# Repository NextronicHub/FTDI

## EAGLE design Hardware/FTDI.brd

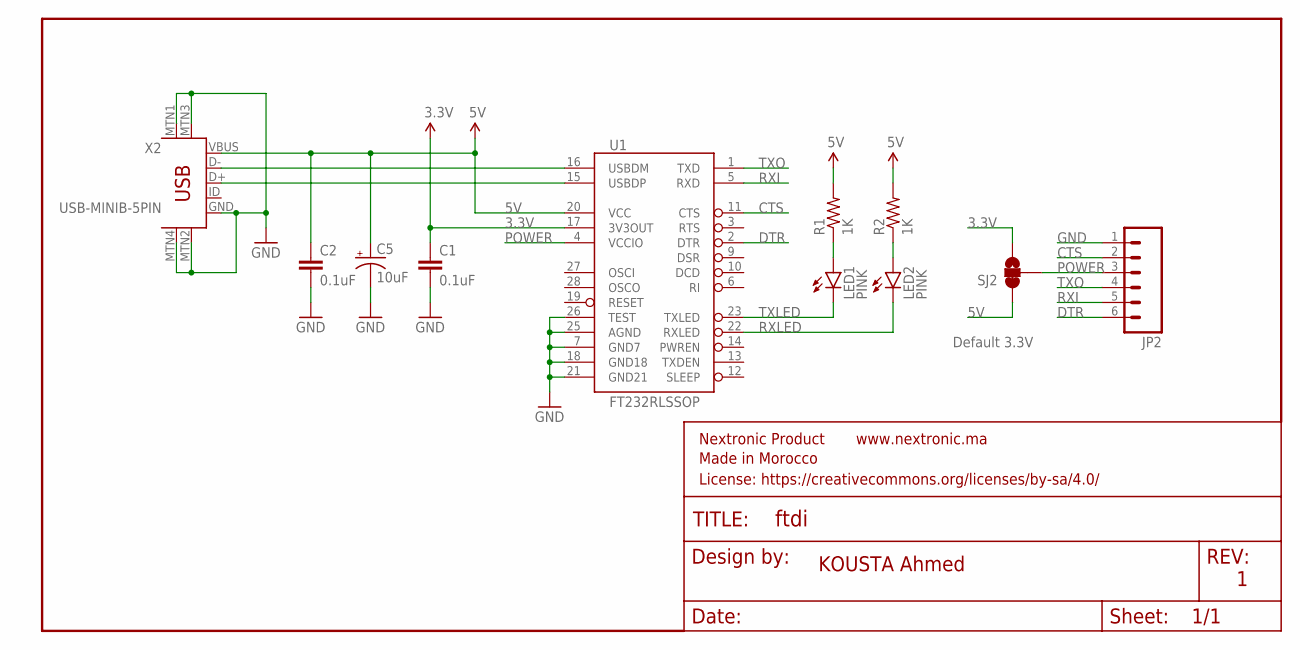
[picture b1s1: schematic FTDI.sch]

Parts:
C1, C2: 0.1uF; 0603-CAP
C5: 10uF; EIA3216
FRAME2: FRAME-LETTER; CREATIVE_COMMONS
JP2: M06SILK_FEMALE_PTH; 1X06
LED1, LED2: PINK; LED-1206
R1, R2: 1K; 0603-RES
SJ2: SOLDERJUMPER_2WAYS; SJ_3
U1: FT232RLSSOP; SSOP28DB
X2: USB-MINIB-5PIN; USB-MINIB

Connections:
3.3V: C1.1, SJ2.3, U1.17 (3V3OUT)
5V: C2.1, C5.A (+), R1.2, R2.2, SJ2.1, U1.20 (VCC), X2.VBUS
CTS: JP2.2, U1.11 (CTS)
DTR: JP2.6, U1.2 (DTR)
GND: C1.2, C2.2, C5.C (-), JP2.1, U1.7 (GND7), U1.18 (GND18), U1.21 (GND21), U1.25 (AGND), U1.26 (TEST), X2.GND, X2.MTN1 (MTN2), X2.MTN2 (MTN3), X2.MTN3 (MTN1), X2.MTN4
unnamed: LED1.A, R1.1
unnamed: LED2.A, R2.1
POWER: JP2.3, SJ2.2, U1.4 (VCCIO)
RXI: JP2.5, U1.5 (RXD)
RXLED: LED2.C, U1.22 (RXLED)
TXLED: LED1.C, U1.23 (TXLED)
TXO: JP2.4, U1.1 (TXD)
USB_D+: U1.15 (USBDP), X2.D+
USB_D-: U1.16 (USBDM), X2.D-

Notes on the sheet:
Default 3.3V
KOUSTA Ahmed

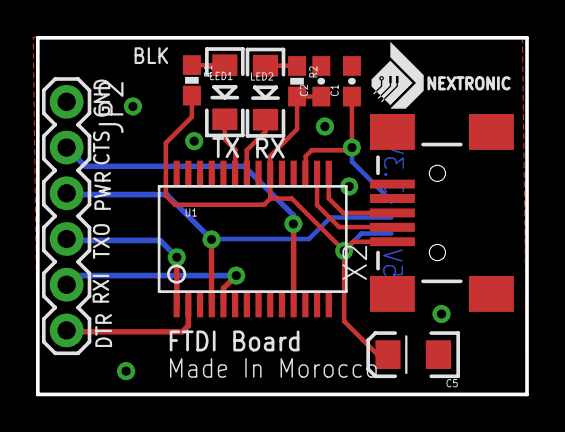
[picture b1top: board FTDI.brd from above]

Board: 2 copper layers, 27.2 x 19.8 mm, 12 parts (1 on the bottom side), 14 nets.

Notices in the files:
parts and their libraries:
SparkFun-Connectors: Licensing: Creative Commons ShareAlike 4.0 International - https://creativecommons.org/licenses/by-sa/4.0
SparkFun-Aesthetics: License: https://creativecommons.org/licenses/by-sa/4.0
